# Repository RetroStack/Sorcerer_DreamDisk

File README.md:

# Exidy Sorcerer/MicroBee DreamDisk - Disk Controller

A Disk Controller for the Exidy Sorcerer and MicroBee, based on the Disk Controller by DreamCards.

See the ["Notes for Testing Dreamdisk PCB.pdf"](http://filebrowser.exidysorcerer.net/) file at the [Exidy Sorcerer forum](https://www.exidysorcerer.net/) on how to setup and test the PCB including the jumpers.

CAUTION: ! This is currently untested !

[Schematics](Latest/Sorcerer_DreamDisk_Rev1_1_Schematics.pdf)

## Gerber Files
- [PCBWay](Latest/Sorcerer_DreamDisk_Rev1_1_Gerber_PCBWay.zip)
- [JLCPCB](Latest/Sorcerer_DreamDisk_Rev1_1_Gerber_JLCPCB.zip)

## Attribution
- Marcel Erz (RetroStack)
- John Halkiadakis
- Michael Borthwick (Exidyboy)

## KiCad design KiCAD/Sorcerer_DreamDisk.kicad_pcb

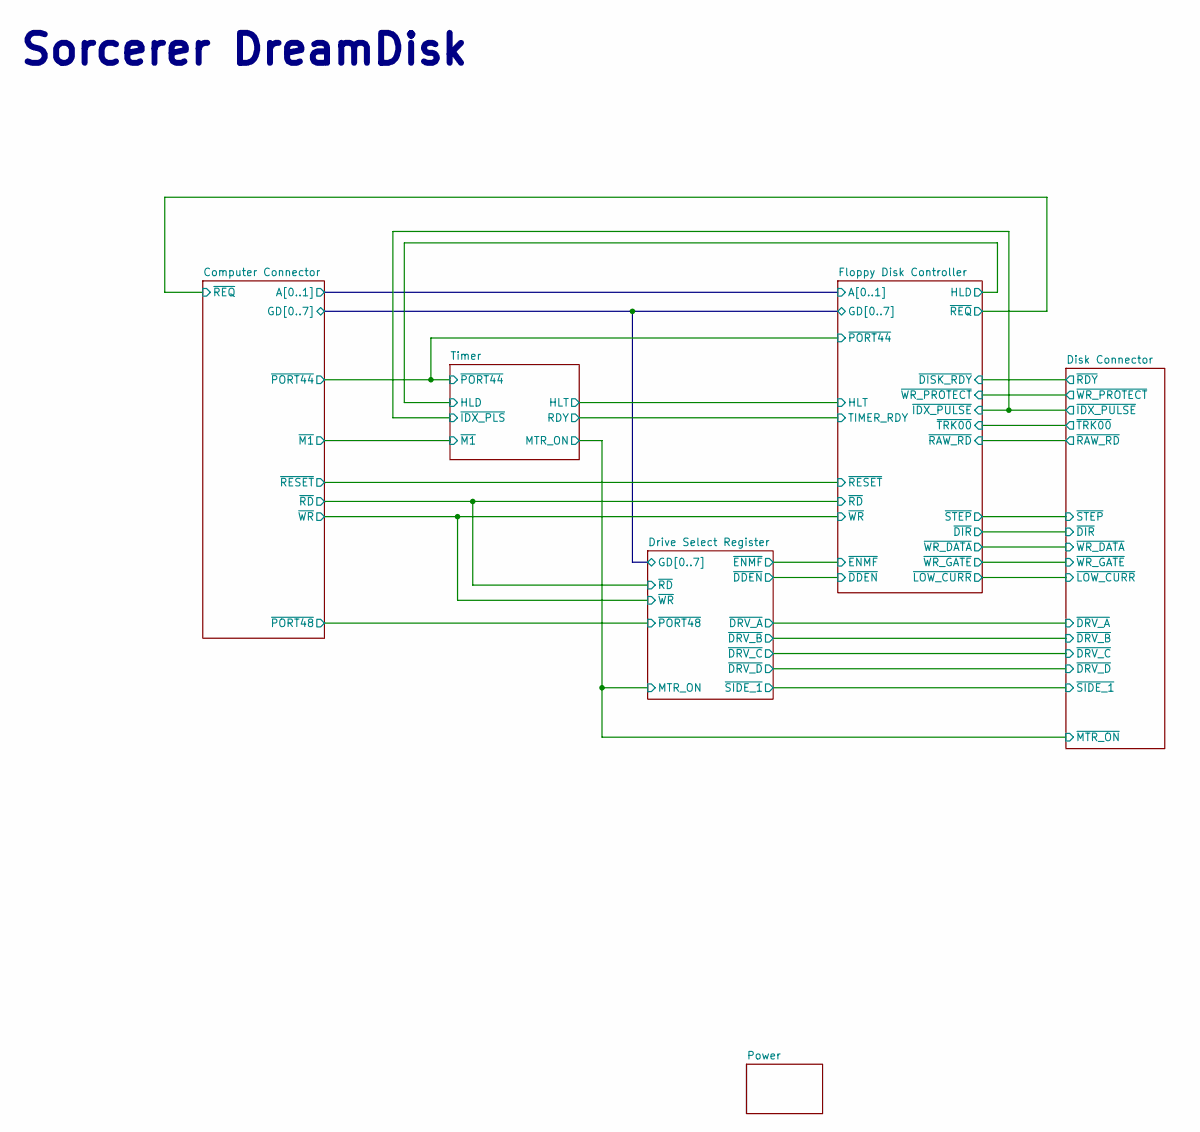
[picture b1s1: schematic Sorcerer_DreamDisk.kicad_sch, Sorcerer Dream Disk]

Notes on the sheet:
Sorcerer DreamDisk

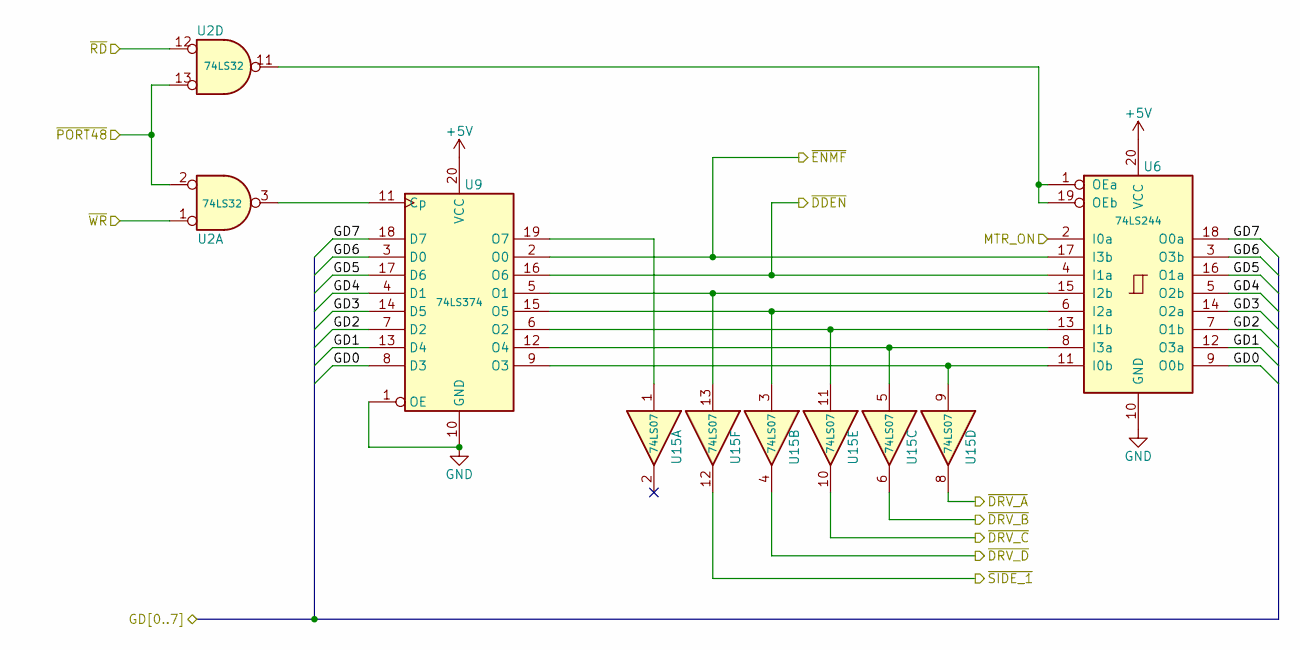
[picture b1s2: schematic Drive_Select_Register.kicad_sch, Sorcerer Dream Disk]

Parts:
U2: 74LS32; DIP-14_W7.62mm
U6: 74LS244; DIP-20_W7.62mm
U9: 74LS374; DIP-20_W7.62mm
U15: 74LS07; DIP-14_W7.62mm

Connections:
+5V: U6.20 (VCC), U9.20 (VCC); also elsewhere on the board
/Computer Connector/BUSDIR: U2.12; also elsewhere on the board
/Computer Connector/GD0: U6.9 (O0b), U9.8 (D3); also elsewhere on the board
/Computer Connector/GD1: U6.12 (O3a), U9.13 (D4); also elsewhere on the board
/Computer Connector/GD2: U6.7 (O1b), U9.7 (D2); also elsewhere on the board
/Computer Connector/GD3: U6.14 (O2a), U9.14 (D5); also elsewhere on the board
/Computer Connector/GD4: U6.5 (O2b), U9.4 (D1); also elsewhere on the board
/Computer Connector/GD5: U6.16 (O1a), U9.17 (D6); also elsewhere on the board
/Computer Connector/GD6: U6.3 (O3b), U9.3 (D0); also elsewhere on the board
/Computer Connector/GD7: U6.18 (O0a), U9.18 (D7); also elsewhere on the board
/Computer Connector/~PORT48: U2.2, U2.13; also elsewhere on the board
/Computer Connector/~S_WR: U2.1; also elsewhere on the board
/Disk Connector/~C_DRV_A: U15.8; also elsewhere on the board
/Disk Connector/~C_DRV_B: U15.6; also elsewhere on the board
/Disk Connector/~C_DRV_C: U15.10; also elsewhere on the board
/Disk Connector/~C_DRV_D: U15.4; also elsewhere on the board
/Disk Connector/~C_SIDE_1: U15.12; also elsewhere on the board
/Disk Connector/~MTR_ON: U6.2 (I0a); also elsewhere on the board
/Drive Select Register/~DDEN: U6.4 (I1a), U9.16 (O6); also elsewhere on the board
/Drive Select Register/~ENMF: U6.17 (I3b), U9.2 (O0); also elsewhere on the board
GND: U6.10 (GND), U9.1 (OE), U9.10 (GND); also elsewhere on the board
unnamed: U6.11 (I0b), U9.9 (O3), U15.9
unnamed: U6.13 (I1b), U9.6 (O2), U15.11
unnamed: U6.6 (I2a), U9.15 (O5), U15.3
unnamed: U6.15 (I2b), U9.5 (O1), U15.13
unnamed: U6.8 (I3a), U9.12 (O4), U15.5
unnamed: U2.11, U6.1 (OEa), U6.19 (OEb)
unnamed: U2.3, U9.11 (Cp)
unnamed: U9.19 (O7), U15.1

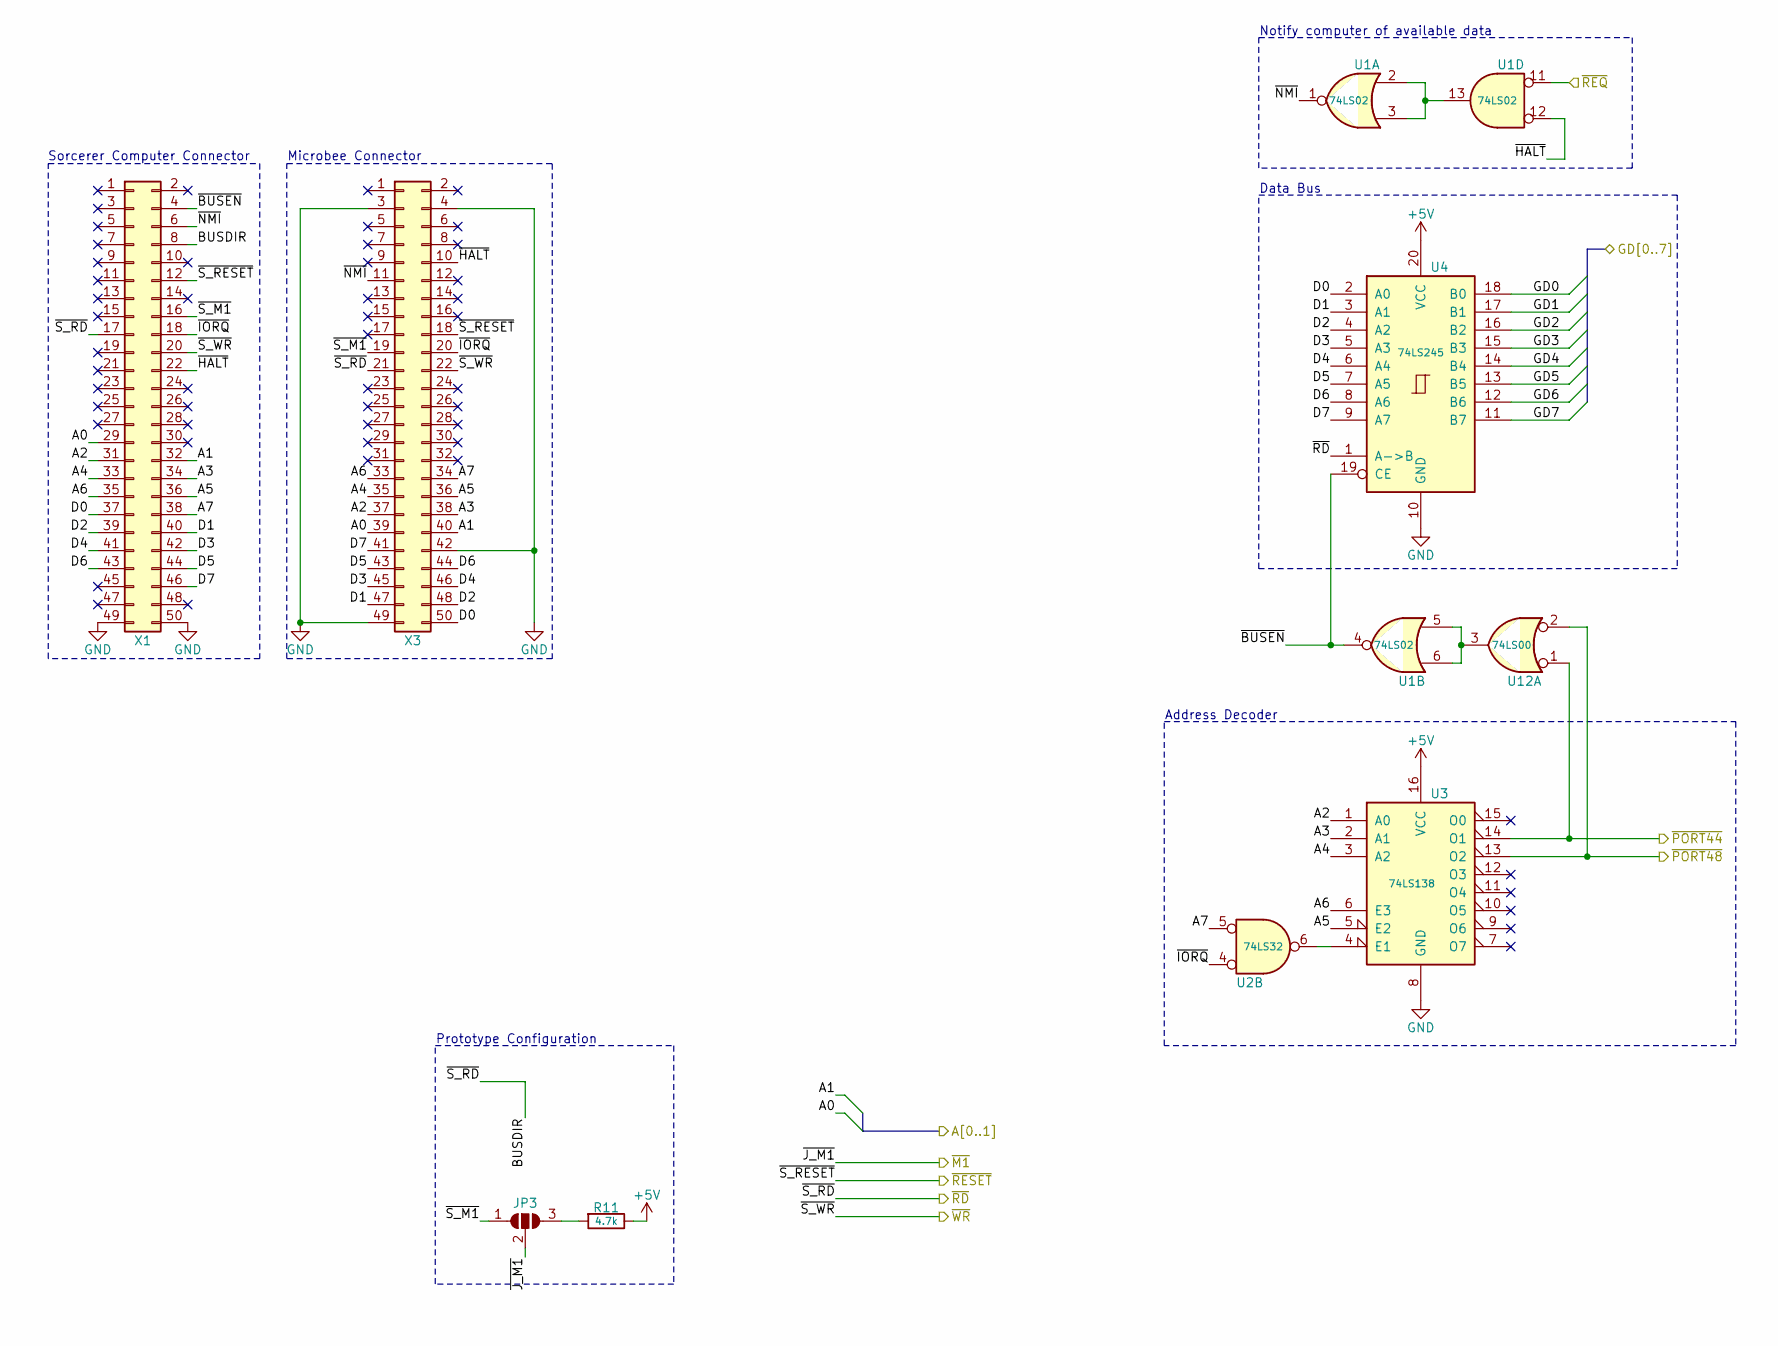
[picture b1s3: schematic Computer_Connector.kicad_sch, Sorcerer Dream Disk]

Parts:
JP3: SolderJumper_3_Open; SolderJumper-3_P1.3mm_Open_RoundedPad1.0x1.5mm_NumberLabels
R11: 4.7k; R_Axial_DIN0207_L6.3mm_D2.5mm_P7.62mm_Horizontal
U1: 74LS02; DIP-14_W7.62mm
U2: 74LS32; DIP-14_W7.62mm
U3: 74LS138; DIP-16_W7.62mm
U4: 74LS245; DIP-20_W7.62mm
U12: 74LS00; DIP-14_W7.62mm
X1, X3: To_Computer; IDC-Header_2x25_P2.54mm_Vertical

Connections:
+5V: R11.1, U3.16 (VCC), U4.20 (VCC); also elsewhere on the board
/Computer Connector/A0: X1.29, X3.39; also elsewhere on the board
/Computer Connector/A1: X1.32, X3.40; also elsewhere on the board
/Computer Connector/A2: U3.1 (A0), X1.31, X3.37
/Computer Connector/A3: U3.2 (A1), X1.34, X3.38
/Computer Connector/A4: U3.3 (A2), X1.33, X3.35
/Computer Connector/A5: U3.5 (E2), X1.36, X3.36
/Computer Connector/A6: U3.6 (E3), X1.35, X3.33
/Computer Connector/A7: U2.5, X1.38, X3.34
/Computer Connector/BUSDIR: U4.1 (A->B), X1.8, X1.17, X3.21; also elsewhere on the board
/Computer Connector/D0: U4.2 (A0), X1.37, X3.50
/Computer Connector/D1: U4.3 (A1), X1.40, X3.47
/Computer Connector/D2: U4.4 (A2), X1.39, X3.48
/Computer Connector/D3: U4.5 (A3), X1.42, X3.45
/Computer Connector/D4: U4.6 (A4), X1.41, X3.46
/Computer Connector/D5: U4.7 (A5), X1.44, X3.43
/Computer Connector/D6: U4.8 (A6), X1.43, X3.44
/Computer Connector/D7: U4.9 (A7), X1.46, X3.41
/Computer Connector/GD0: U4.18 (B0); also elsewhere on the board
/Computer Connector/GD1: U4.17 (B1); also elsewhere on the board
/Computer Connector/GD2: U4.16 (B2); also elsewhere on the board
/Computer Connector/GD3: U4.15 (B3); also elsewhere on the board
/Computer Connector/GD4: U4.14 (B4); also elsewhere on the board
/Computer Connector/GD5: U4.13 (B5); also elsewhere on the board
/Computer Connector/GD6: U4.12 (B6); also elsewhere on the board
/Computer Connector/GD7: U4.11 (B7); also elsewhere on the board
/Computer Connector/~BUSEN: U1.4, U4.19 (CE), X1.4
/Computer Connector/~HALT: U1.12, X1.22, X3.10
/Computer Connector/~IORQ: U2.4, X1.18, X3.20
/Computer Connector/~J_M1: JP3.2 (C); also elsewhere on the board
/Computer Connector/~NMI: U1.1, X1.6, X3.11
/Computer Connector/~PORT44: U3.14 (O1), U12.1; also elsewhere on the board
/Computer Connector/~PORT48: U3.13 (O2), U12.2; also elsewhere on the board
/Computer Connector/~REQ: U1.11; also elsewhere on the board
/Computer Connector/~S_M1: JP3.1 (A), X1.16, X3.19
/Computer Connector/~S_RESET: X1.12, X3.18; also elsewhere on the board
/Computer Connector/~S_WR: X1.20, X3.22; also elsewhere on the board
GND: U3.8 (GND), U4.10 (GND), X1.49, X1.50, X3.3, X3.4, X3.42, X3.49; also elsewhere on the board
unnamed: JP3.3 (B), R11.2
unnamed: U1.5, U1.6, U12.3
unnamed: U1.2, U1.3, U1.13
unnamed: U2.6, U3.4 (E1)

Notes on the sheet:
Prototype Configuration
Sorcerer Computer Connector
Data Bus
Address Decoder
Microbee Connector
Notify computer of available data

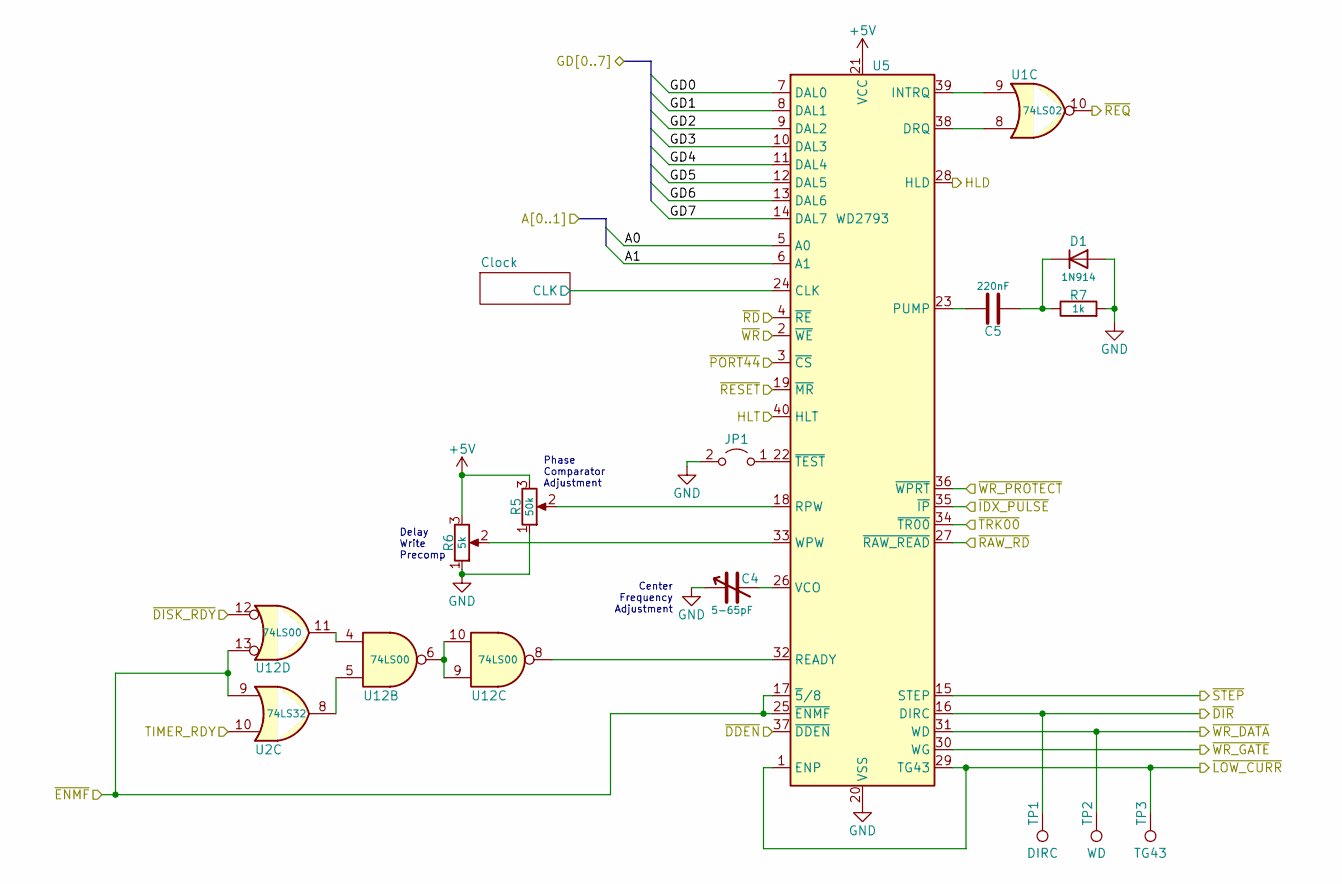
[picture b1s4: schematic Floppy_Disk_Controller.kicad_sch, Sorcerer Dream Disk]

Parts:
C4: 5-65pF; C_Trim (BFC2 808 32659)
C5: 220nF; C_Disc_D5.0mm_W2.5mm_P2.50mm
D1: 1N914; D_DO-35_SOD27_P7.62mm_Horizontal
JP1: Jumper_2_Open; PinHeader_1x02_P2.54mm_Vertical
R5: 50k; Potentiometer_Bourns_3296W_Vertical
R6: 5k; R_Pot (Bourns 3306P)
R7: 1k; R_Axial_DIN0207_L6.3mm_D2.5mm_P7.62mm_Horizontal
TP1: DIRC; TestPoint_Pad_D2.0mm
TP2: WD; TestPoint_Pad_D2.0mm
TP3: TG43; TestPoint_Pad_D2.0mm
U1: 74LS02; DIP-14_W7.62mm
U2: 74LS32; DIP-14_W7.62mm
U5: WD2793; DIP-40_W15.24mm
U12: 74LS00; DIP-14_W7.62mm

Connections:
+5V: R5.3, R6.3, U5.21 (VCC); also elsewhere on the board
/Computer Connector/A0: U5.5 (A0); also elsewhere on the board
/Computer Connector/A1: U5.6 (A1); also elsewhere on the board
/Computer Connector/BUSDIR: U5.4 (~RE); also elsewhere on the board
/Computer Connector/GD0: U5.7 (DAL0); also elsewhere on the board
/Computer Connector/GD1: U5.8 (DAL1); also elsewhere on the board
/Computer Connector/GD2: U5.9 (DAL2); also elsewhere on the board
/Computer Connector/GD3: U5.10 (DAL3); also elsewhere on the board
/Computer Connector/GD4: U5.11 (DAL4); also elsewhere on the board
/Computer Connector/GD5: U5.12 (DAL5); also elsewhere on the board
/Computer Connector/GD6: U5.13 (DAL6); also elsewhere on the board
/Computer Connector/GD7: U5.14 (DAL7); also elsewhere on the board
/Computer Connector/~PORT44: U5.3 (~CS); also elsewhere on the board
/Computer Connector/~REQ: U1.10; also elsewhere on the board
/Computer Connector/~S_RESET: U5.19 (~MR); also elsewhere on the board
/Computer Connector/~S_WR: U5.2 (~WE); also elsewhere on the board
/Disk Connector/~DIR: TP1.1, U5.16 (DIRC); also elsewhere on the board
/Disk Connector/~IDX_PULSE: U5.35 (~IP); also elsewhere on the board
/Disk Connector/~LOW_CURR: TP3.1, U5.1 (ENP), U5.29 (TG43); also elsewhere on the board
/Disk Connector/~RAW_RD: U5.27 (~RAW_READ); also elsewhere on the board
/Disk Connector/~RDY: U12.12; also elsewhere on the board
/Disk Connector/~STEP: U5.15 (STEP); also elsewhere on the board
/Disk Connector/~TRK00: U5.34 (~TR00); also elsewhere on the board
/Disk Connector/~WR_DATA: TP2.1, U5.31 (WD); also elsewhere on the board
/Disk Connector/~WR_GATE: U5.30 (WG); also elsewhere on the board
/Disk Connector/~WR_PROTECT: U5.36 (~WPRT); also elsewhere on the board
/Drive Select Register/~DDEN: U5.37 (~DDEN); also elsewhere on the board
/Drive Select Register/~ENMF: U2.9, U5.17 (~5/8), U5.25 (~ENMF), U12.13; also elsewhere on the board
/Floppy Disk Controller/Clock/CLK: U5.24 (CLK); also elsewhere on the board
/Floppy Disk Controller/HLD: U5.28 (HLD); also elsewhere on the board
/Floppy Disk Controller/HLT: U5.40 (HLT); also elsewhere on the board
/Floppy Disk Controller/TIMER_RDY: U2.10; also elsewhere on the board
GND: C4.1, D1.2 (A), JP1.2 (B), R5.1, R6.1, R7.2, U5.20 (VSS); also elsewhere on the board
unnamed: C5.2, D1.1 (K), R7.1
unnamed: JP1.1 (A), U5.22 (~TEST)
unnamed: U1.8, U5.38 (DRQ)
unnamed: U1.9, U5.39 (INTRQ)
unnamed: C5.1, U5.23 (PUMP)
unnamed: U5.32 (READY), U12.8
unnamed: R5.2, U5.18 (RPW)
unnamed: C4.2, U5.26 (VCO)
unnamed: R6.2, U5.33 (WPW)
unnamed: U2.8, U12.5
unnamed: U12.6, U12.9, U12.10
unnamed: U12.4, U12.11

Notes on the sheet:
Center Frequency Adjustment
Delay Write Precomp
Phase Comparator Adjustment

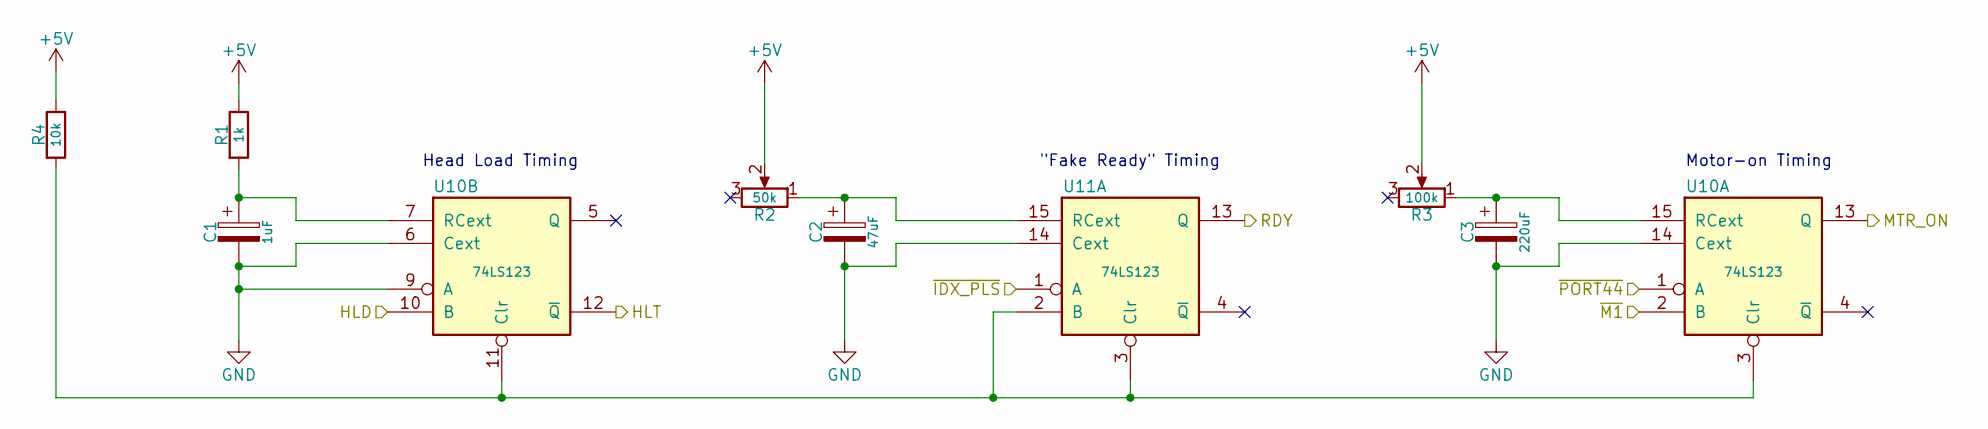
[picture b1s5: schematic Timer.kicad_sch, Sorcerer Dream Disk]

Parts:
C1: 1uF; CP_Radial_D5.0mm_P2.00mm
C2: 47uF; CP_Radial_D5.0mm_P2.00mm
C3: 220uF; CP_Radial_D6.3mm_P2.50mm
R1: 1k; R_Axial_DIN0207_L6.3mm_D2.5mm_P7.62mm_Horizontal
R2: 50k; R_Pot (Bourns 3306P)
R3: 100k; R_Pot (Bourns 3306P)
R4: 10k; R_Axial_DIN0207_L6.3mm_D2.5mm_P7.62mm_Horizontal
U10, U11: 74LS123; DIP-16_W7.62mm

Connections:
+5V: R1.1, R2.2, R3.2, R4.1; also elsewhere on the board
/Computer Connector/~J_M1: U10.2 (B); also elsewhere on the board
/Computer Connector/~PORT44: U10.1 (A); also elsewhere on the board
/Disk Connector/~IDX_PULSE: U11.1 (A); also elsewhere on the board
/Disk Connector/~MTR_ON: U10.13 (Q); also elsewhere on the board
/Floppy Disk Controller/HLD: U10.10 (B); also elsewhere on the board
/Floppy Disk Controller/HLT: U10.12 (~Q); also elsewhere on the board
/Floppy Disk Controller/TIMER_RDY: U11.13 (Q); also elsewhere on the board
GND: C1.2, C2.2, C3.2, U10.6 (Cext), U10.9 (A), U10.14 (Cext), U11.14 (Cext); also elsewhere on the board
unnamed: R4.2, U10.3 (Clr), U10.11 (Clr), U11.2 (B), U11.3 (Clr)
unnamed: C3.1, R3.1, U10.15 (RCext)
unnamed: C1.1, R1.2, U10.7 (RCext)
unnamed: C2.1, R2.1, U11.15 (RCext)

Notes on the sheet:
"Fake Ready" Timing
Head Load Timing
Motor-on Timing

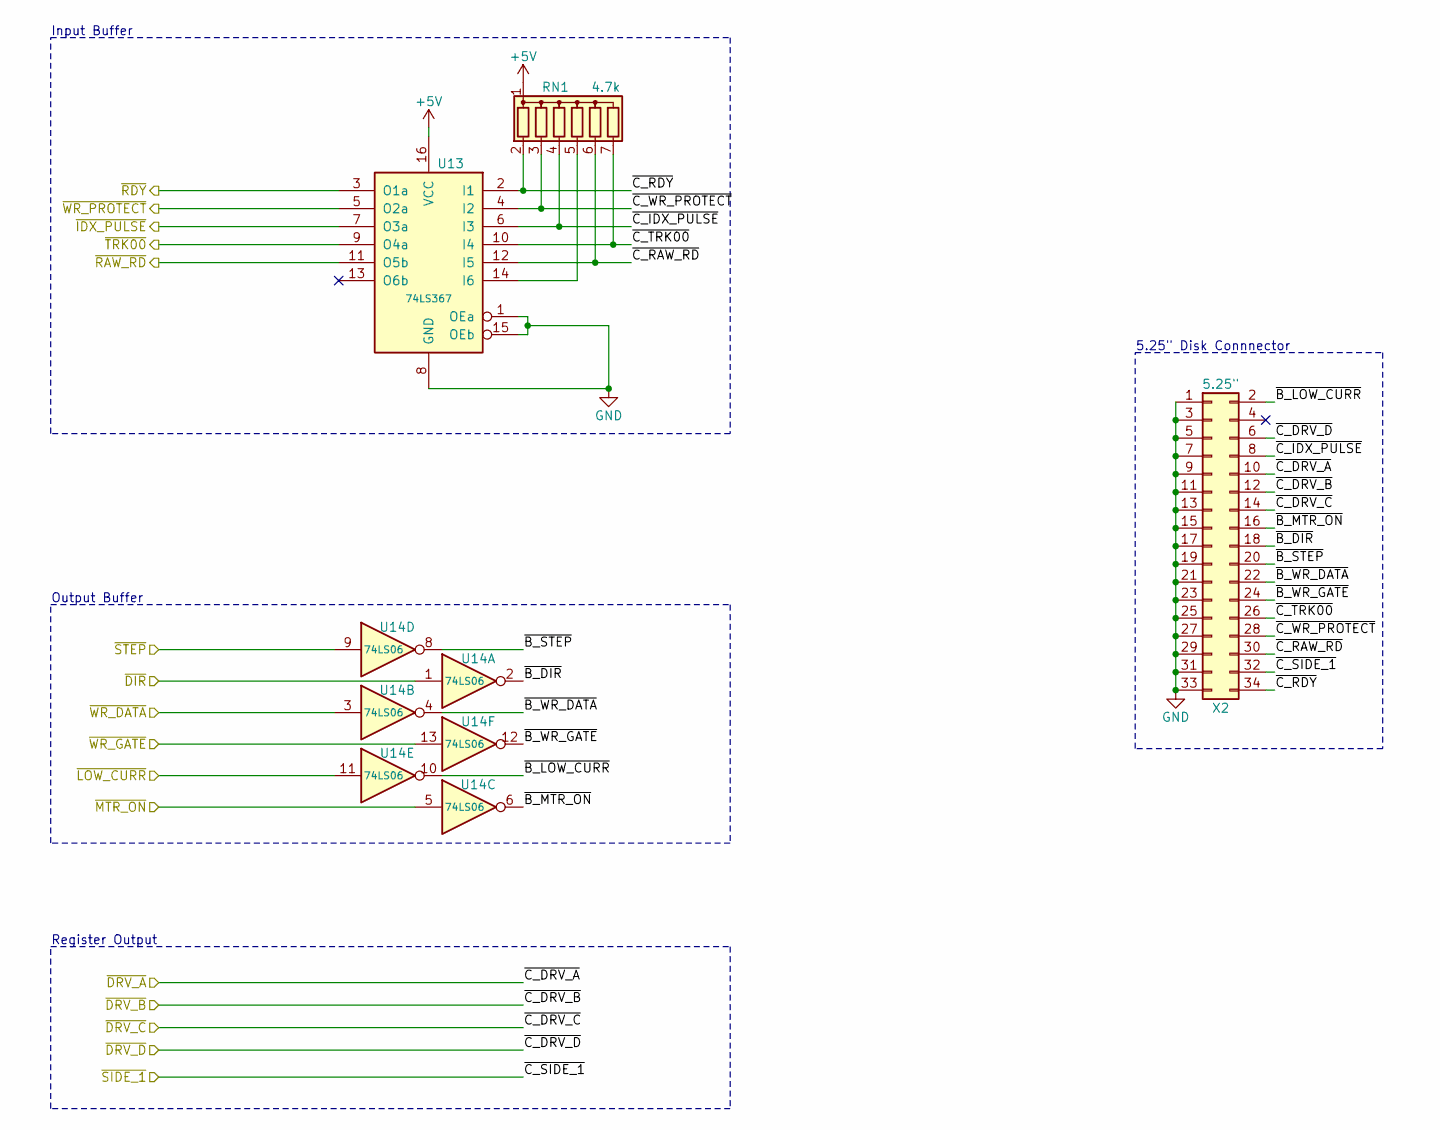
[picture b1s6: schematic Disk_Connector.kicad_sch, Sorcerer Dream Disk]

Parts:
RN1: 4.7k; R_Array_SIP7
U13: 74LS367; DIP-16_W7.62mm
U14: 74LS06; DIP-14_W7.62mm
X2: 5.25"; IDC-Header_2x17_P2.54mm_Vertical

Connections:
+5V: RN1.1 (common), U13.16 (VCC); also elsewhere on the board
/Disk Connector/~B_DIR: U14.2, X2.18
/Disk Connector/~B_LOW_CURR: U14.10, X2.2
/Disk Connector/~B_MTR_ON: U14.6, X2.16
/Disk Connector/~B_STEP: U14.8, X2.20
/Disk Connector/~B_WR_DATA: U14.4, X2.22
/Disk Connector/~B_WR_GATE: U14.12, X2.24
/Disk Connector/~C_DRV_A: X2.10; also elsewhere on the board
/Disk Connector/~C_DRV_B: X2.12; also elsewhere on the board
/Disk Connector/~C_DRV_C: X2.14; also elsewhere on the board
/Disk Connector/~C_DRV_D: X2.6; also elsewhere on the board
/Disk Connector/~C_IDX_PULSE: RN1.4 (R3), U13.6 (I3), X2.8
/Disk Connector/~C_RAW_RD: RN1.6 (R5), U13.12 (I5), X2.30
/Disk Connector/~C_RDY: RN1.2 (R1), U13.2 (I1), X2.34
/Disk Connector/~C_SIDE_1: X2.32; also elsewhere on the board
/Disk Connector/~C_TRK00: RN1.7 (R6), U13.10 (I4), X2.26
/Disk Connector/~C_WR_PROTECT: RN1.3 (R2), U13.4 (I2), X2.28
/Disk Connector/~DIR: U14.1; also elsewhere on the board
/Disk Connector/~IDX_PULSE: U13.7 (O3a); also elsewhere on the board
/Disk Connector/~LOW_CURR: U14.11; also elsewhere on the board
/Disk Connector/~MTR_ON: U14.5; also elsewhere on the board
/Disk Connector/~RAW_RD: U13.11 (O5b); also elsewhere on the board
/Disk Connector/~RDY: U13.3 (O1a); also elsewhere on the board
/Disk Connector/~STEP: U14.9; also elsewhere on the board
/Disk Connector/~TRK00: U13.9 (O4a); also elsewhere on the board
/Disk Connector/~WR_DATA: U14.3; also elsewhere on the board
/Disk Connector/~WR_GATE: U14.13; also elsewhere on the board
/Disk Connector/~WR_PROTECT: U13.5 (O2a); also elsewhere on the board
GND: U13.1 (OEa), U13.8 (GND), U13.15 (OEb), X2.1, X2.3, X2.5, X2.7, X2.9, X2.11, X2.13, X2.15, X2.17, X2.19, X2.21, X2.23, X2.25, X2.27, X2.29, X2.31, X2.33; also elsewhere on the board
unnamed: RN1.5 (R4), U13.14 (I6)

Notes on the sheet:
Register Output
5.25" Disk Connnector
Input Buffer
Output Buffer

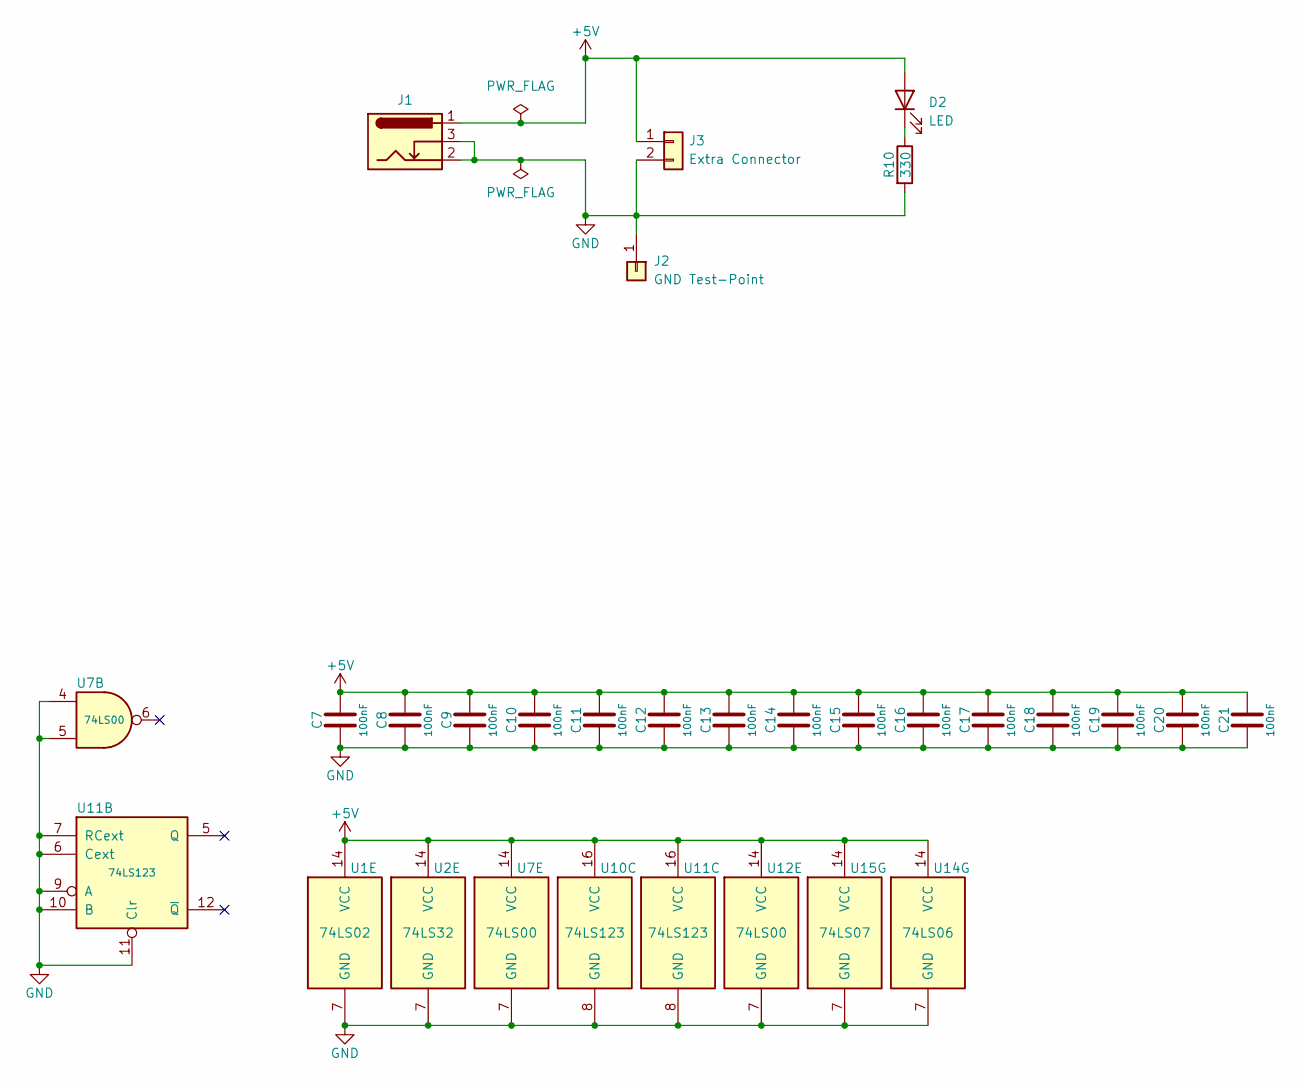
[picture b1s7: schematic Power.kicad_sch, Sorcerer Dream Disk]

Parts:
C7, C8, C9, C10, C11, C12, C13, C14, C15, C16, C17, C18, C19, C20, C21: 100nF; C_Disc_D3.8mm_W2.6mm_P2.50mm
D2: LED; LED_D3.0mm
J1: 5V; BarrelJack_Horizontal
J2: GND Test-Point; PinHeader_1x01_P2.54mm_Vertical
J3: Extra Connector; PinHeader_1x02_P2.54mm_Vertical
R10: 330; R_Axial_DIN0207_L6.3mm_D2.5mm_P7.62mm_Horizontal
U1: 74LS02; DIP-14_W7.62mm
U2: 74LS32; DIP-14_W7.62mm
U7, U12: 74LS00; DIP-14_W7.62mm
U10, U11: 74LS123; DIP-16_W7.62mm
U14: 74LS06; DIP-14_W7.62mm
U15: 74LS07; DIP-14_W7.62mm

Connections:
+5V: C7.2, C8.2, C9.2, C10.2, C11.2, C12.2, C13.2, C14.2, C15.2, C16.2, C17.2, C18.2, C19.2, C20.2, C21.2, D2.2 (A), J1.1, J3.1, U1.14 (VCC), U2.14 (VCC), U7.14 (VCC), U10.16 (VCC), U11.16 (VCC), U12.14 (VCC), U14.14 (VCC), U15.14 (VCC); also elsewhere on the board
GND: C7.1, C8.1, C9.1, C10.1, C11.1, C12.1, C13.1, C14.1, C15.1, C16.1, C17.1, C18.1, C19.1, C20.1, C21.1, J1.2, J1.3, J2.1, J3.2, R10.2, U1.7 (GND), U2.7 (GND), U7.4, U7.5, U7.7 (GND), U10.8 (GND), U11.6 (Cext), U11.7 (RCext), U11.8 (GND), U11.9 (A), U11.10 (B), U11.11 (Clr), U12.7 (GND), U14.7 (GND), U15.7 (GND); also elsewhere on the board
unnamed: D2.1 (K), R10.1

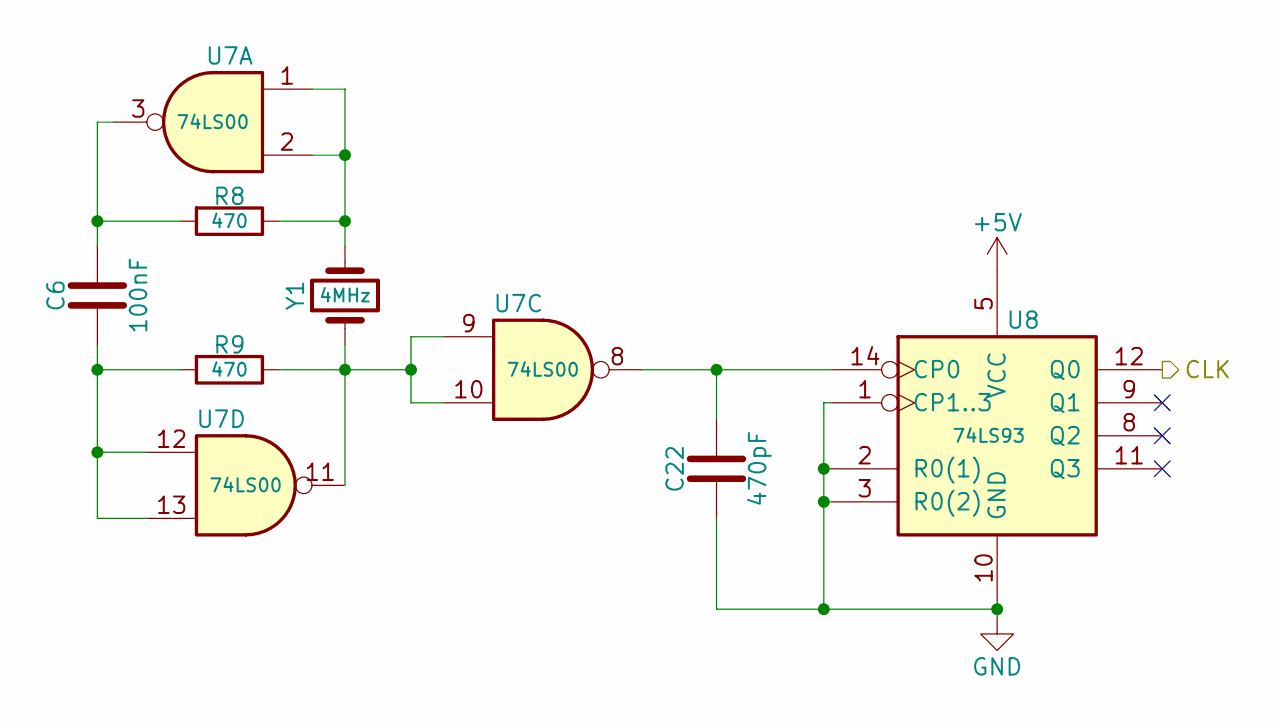
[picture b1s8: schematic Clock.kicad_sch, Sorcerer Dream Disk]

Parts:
C6: 100nF; C_Disc_D3.8mm_W2.6mm_P2.50mm
C22: 470pF; C_Disc_D3.8mm_W2.6mm_P2.50mm
R8, R9: 470; R_Axial_DIN0207_L6.3mm_D2.5mm_P7.62mm_Horizontal
U7: 74LS00; DIP-14_W7.62mm
U8: 74LS93; DIP-14_W7.62mm
Y1: 4MHz; Crystal_HC49-U_Vertical

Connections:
+5V: U8.5 (VCC); also elsewhere on the board
/Floppy Disk Controller/Clock/CLK: U8.12 (Q0); also elsewhere on the board
GND: C22.2, U8.1 (CP1..3), U8.2 (R0(1)), U8.3 (R0(2)), U8.10 (GND); also elsewhere on the board
unnamed: C6.1, R8.2, U7.3
unnamed: C6.2, R9.2, U7.12, U7.13
unnamed: R8.1, U7.1, U7.2, Y1.2
unnamed: R9.1, U7.9, U7.10, U7.11, Y1.1
unnamed: C22.1, U7.8, U8.14 (CP0)

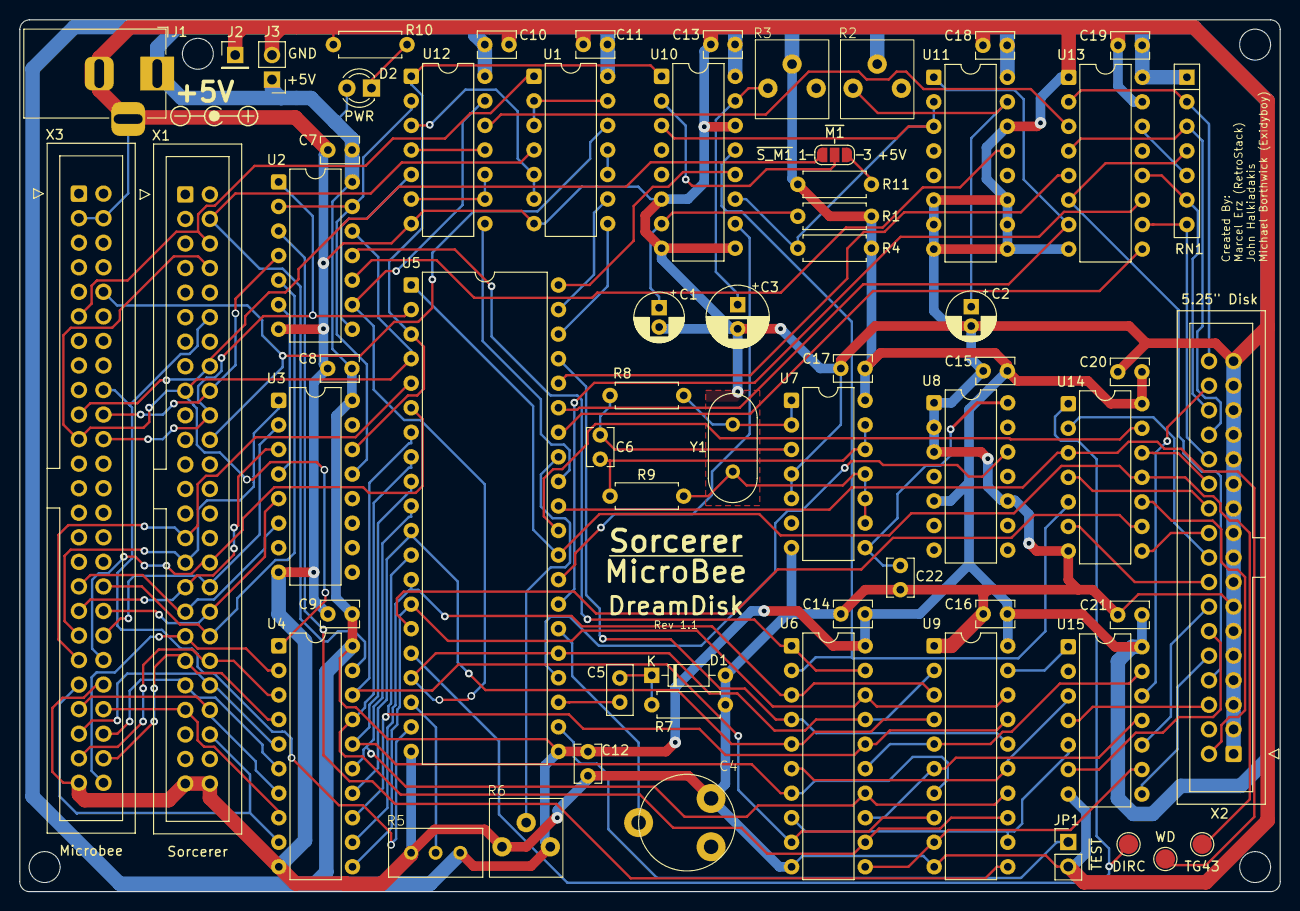
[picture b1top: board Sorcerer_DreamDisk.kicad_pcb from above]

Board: 2 copper layers, 130.4 x 90.2 mm, 63 parts (0 on the bottom side), 106 nets.

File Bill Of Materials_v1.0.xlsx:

Mouser No | Mfr. No | Manufacturer | PCB Layout | Description | Order Qty. | Price (AUD) | Ext.: (AUD)
810-FG14X7R1H224KNT0 | FG14X7R1H224KNT00 | TDK | C5 | Multilayer Ceramic Capacitors MLCC - Leaded RAD 50V 0.22uF X7R 10% LS:2.5mm | 1 | $0.47 | $0.47
594-K104K10X7RF53H5 | K104K10X7RF53H5 | Vishay | C6, C8-C21 | Multilayer Ceramic Capacitors MLCC - Leaded 0.1uF 50V 10% X7R 5mm LS | 16 | $0.167 | $2.67
603-MFR-25FBF52-4K7 | MFR-25FBF52-4K7 | YAGEO | R11 | Metal Film Resistors - Through Hole 4.7K OHM 1/4W 1% | 1 | $0.162 | $0.16
603-MFR-25FRF52-470R | MFR-25FRF52-470R | YAGEO | R8, R9 | Metal Film Resistors - Through Hole 470 OHM 1/4W 1% | 2 | $0.162 | $0.32
603-MFR-25FRE52-1K | MFR-25FRE52-1K | YAGEO | R1, R7 | Metal Film Resistors - Through Hole 1Kohm 1% 1/4W Metal Film Resistor | 2 | $0.162 | $0.32
603-MFR-25FRF5210K | MFR-25FRF52-10K | YAGEO | R4 | Metal Film Resistors - Through Hole 10 kOhms 250 mW 1% 100 PPM / C | 1 | $0.162 | $0.16
652-4607X-1LF-4.7K | 4607X-101-472LF | Bourns | RN1 | Resistor Networks & Arrays 7pins 4.7Kohms Bussed | 1 | $0.81 | $0.81
595-SN74LS02N | SN74LS02N | Texas Instruments | U1 | Logic Gates Quad 2-Input | 1 | $0.891 | $0.89
595-SN74LS32N | SN74LS32N | Texas Instruments | U2 | Logic Gates Quad 2-Input | 1 | $0.907 | $0.91
595-SN74LS138N | SN74LS138N | Texas Instruments | U3 | Encoders, Decoders, Multiplexers & Demultiplexers Line Decoder | 1 | $1.13 | $1.13
595-SN74LS245N | SN74LS245N | Texas Instruments | U4 | Bus Transceivers Octal Bus | 1 | $2.01 | $2.01
595-SN74LS244N | SN74LS244N | Texas Instruments | U6 | Buffers & Line Drivers Tri-State Octal | 1 | $1.88 | $1.88
595-SN74LS00N | SN74LS00N | Texas Instruments | U7, U12 | Logic Gates Quad 2-In Pos NAND | 2 | $0.923 | $1.85
512-1N914TR | 1N914TR | onsemi | D1 | Diodes - General Purpose, Power, Switching Hi Conductance Fast | 1 | $0.162 | $0.16
649-67998-400HLF | 67998-400HLF | Amphenol | JP1 TEST | Headers & Wire Housings .100CC STR HEADER | 1 | $0.162 | $0.16
710-860020672005 | 860020672005 | Wurth Elektronik | C1 | Aluminium Electrolytic Capacitors - Radial Leaded WCAP-ATG5 1uF 50V 20% Radial | 1 | $0.162 | $0.16
710-860020472006 | 860020472006 | Wurth Elektronik | C2 | Aluminium Electrolytic Capacitors - Radial Leaded WCAP-ATG5 47uF 25V 20% Radial | 1 | $0.162 | $0.16
710-860010273009 | 860010273009 | Wurth Elektronik | C3 | Aluminium Electrolytic Capacitors - Radial Leaded WCAP-ATG8 220uF 10V 20% Radial | 1 | $0.243 | $0.24
595-SN74LS374N | SN74LS374N | Texas Instruments | U9 | Flip-Flops Octal | 1 | $2.01 | $2.01
595-SN74LS123N | SN74LS123N | Texas Instruments | U10, U11 | Monostable Multi-vibrator Dual Mono | 2 | $1.30 | $2.60
595-SN74LS367AN | SN74LS367AN | Texas Instruments | U13 | Buffers & Line Drivers Hex Bus Drivers With 3-State Outputs | 1 | $2.33 | $2.33
595-SN74LS06N | SN74LS06N | Texas Instruments | U14 | Buffers & Line Drivers Hex inverter Buffer/ Driver | 1 | $1.49 | $1.49
571-5103308-7 | 5103308-7 | TE Connectivity | X2 | Headers & Wire Housings 34P HEADER | 1 | $6.04 | $6.04
571-1-5103308-0 | 1-5103308-0 | TE Connectivity | X1 | Headers & Wire Housings 50P HEADER SP 15DP | 1 | $6.66 | $6.66
652-3306P-1-503 | 3306P-1-503 | Bourns | R2 ,R5 | Trimmer Resistors - Through Hole 50K 25% 6mm Single Turn | 2 | $0.713 | $1.43
652-3306P-1-502 | 3306P-1-502 | Bourns | R6 (ONLY for 8") | Trimmer Resistors - Through Hole 5K 25% 6mm Single Turn | 1 | $0.761 | $0.76
652-3306P-1-104 | 3306P-1-104 | Bourns | R3 | Trimmer Resistors - Through Hole 100K 25% 6mm Single Turn | 1 | $0.794 | $0.79
73-XT49S400-20 | XT9S20ANA4M | Vishay | Y1 | Crystals 4MHz 20pF | 1 | $0.778 | $0.78
474-PRT-10811 | PRT-10811 | SparkFun Electronics | J1 | SparkFun Accessories DC Barrel Jack Adapter - Breadboard Compatible | 1 | $1.54 | $1.54
595-SN74LS07N | SN74LS07N | Texas Instruments | U15 | Buffers & Line Drivers Hex W/ OC HV Out | 1 | $1.15 | $1.15
594-2222-808-32659 | BFC280832659 | Vishay | C4 (VCO ADJ) | Trimmer/Variable Capacitors TRIMMER CAPACITOR (5.5 pF to 65 pF) | 1 | $9.98 | $9.98
595-SN74LS93N | SN74LS93N | Texas Instruments | U8 | Counter ICs 4bit Binary | 1 | $4.92 | $4.92
WD2793 | N/A | N/A | U5 | Western Digital 2793 Floppy Disk Controller

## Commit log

2023-12-18 Initial Commit for Revision 1.0
2023-12-18 Update README.md with Untested Comment
2023-12-18 Update README.md - More details
2023-12-18 Create LICENSE
2024-05-20 Update LICENSE
2025-05-12 Updated revision for Rev 1.1
    Adding test points
    Additional power source connectors
    LED for Power Indicator
    Fix for clock (additional capacitor)
    Microbee connector
    Removal of unused BUSDIR solder jumpers
2025-05-12 Update image
2025-05-12 Update silkscreen label for MicroBee
